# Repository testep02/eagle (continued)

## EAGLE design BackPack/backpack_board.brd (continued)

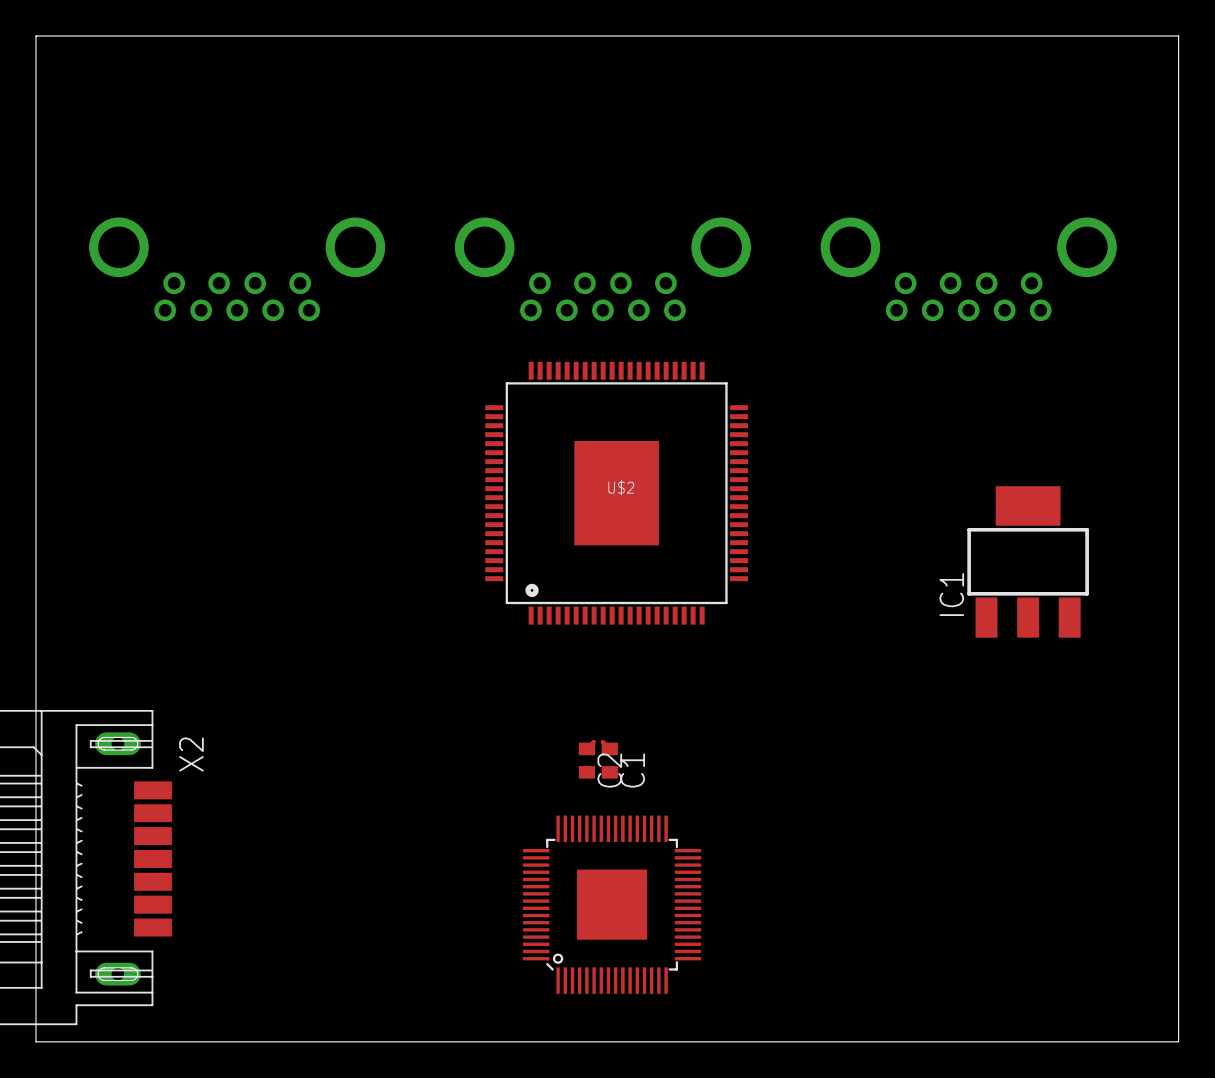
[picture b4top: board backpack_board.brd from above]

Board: 4 copper layers, 63.5 x 55.9 mm, 9 parts (0 on the bottom side), 14 nets.

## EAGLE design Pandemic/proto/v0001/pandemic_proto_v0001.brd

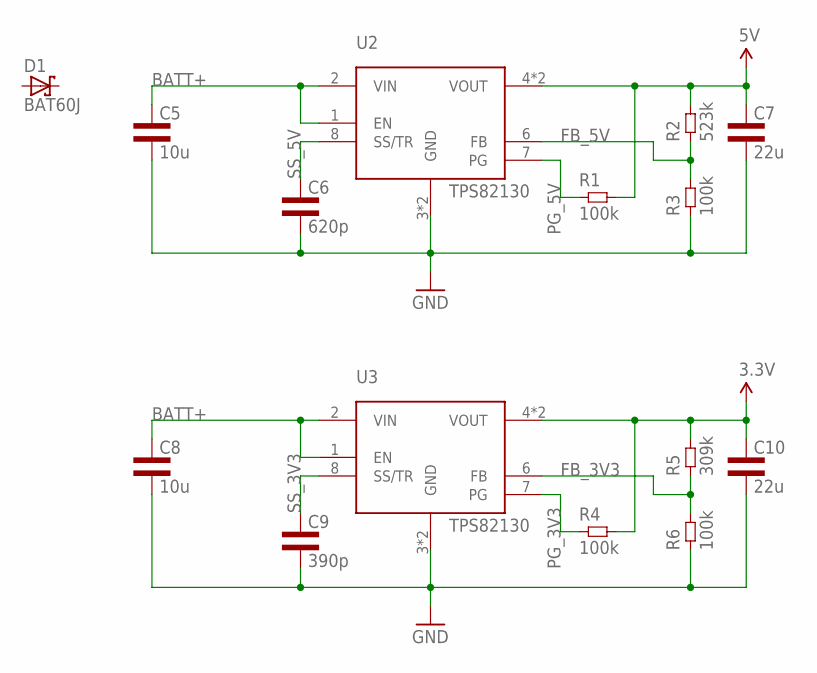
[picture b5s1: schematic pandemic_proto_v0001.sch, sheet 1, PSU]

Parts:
C5, C8: 10u; 1206L3
C6: 620p; 0402L3
C7, C10: 22u; 0805L3
C9: 390p; 0402L3
D1: BAT60J; SOD323_ST
R1, R4: 100k; 0402L3
R2: 523k; 0402L3
R3, R6: 100k; 0805L3
R5: 309k; 0402L3
U2, U3: TPS82130; SIL0008C

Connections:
3.3V: C10.1, R4.P$2 (2), R5.P$2 (2), U3.4 (VOUT), U3.5 (VOUT); also elsewhere on the board
5V: C7.1, R1.P$2 (2), R2.P$2 (2), U2.4 (VOUT), U2.5 (VOUT)
BATT+: C5.1, C8.1, U2.1 (EN), U2.2 (VIN), U3.1 (EN), U3.2 (VIN); also elsewhere on the board
FB_3V3: R5.P$1 (1), R6.2, U3.6 (FB)
FB_5V: R2.P$1 (1), R3.2, U2.6 (FB)
GND: C5.2, C6.P$2 (2), C7.2, C8.2, C9.P$2 (2), C10.2, R3.1, R6.1, U2.3 (GND), U2.TP (GND), U3.3 (GND), U3.TP (GND); also elsewhere on the board
PG_3V3: R4.P$1 (1), U3.7 (PG)
PG_5V: R1.P$1 (1), U2.7 (PG)
SS_3V3: C9.P$1 (1), U3.8 (SS/TR)
SS_5V: C6.P$1 (1), U2.8 (SS/TR)

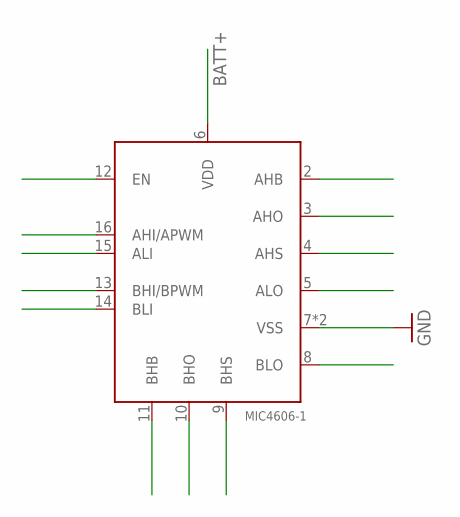
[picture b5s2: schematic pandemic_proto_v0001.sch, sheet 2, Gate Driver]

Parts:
MD1: MIC4606-1; QFN44-16LD-PL-2

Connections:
BATT+: MD1.6 (VDD); also elsewhere on the board
GND: MD1.7 (VSS), MD1.TP (VSS); also elsewhere on the board

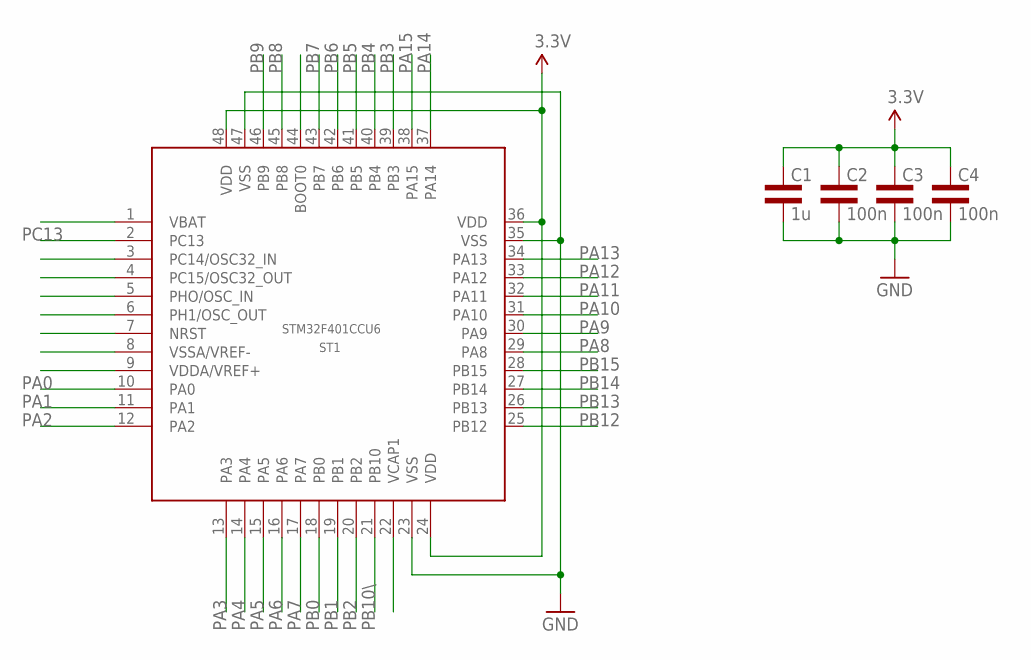
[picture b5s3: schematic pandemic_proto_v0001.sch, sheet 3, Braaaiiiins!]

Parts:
C1: 1u; 0805L3
C2, C3, C4: 100n; 0402L3
ST1: STM32F401CCU6; UFQFPN48

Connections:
3.3V: C1.1, C2.P$1 (1), C3.P$1 (1), C4.P$1 (1), ST1.24 (VDD), ST1.36 (VDD), ST1.48 (VDD); also elsewhere on the board
GND: C1.2, C2.P$2 (2), C3.P$2 (2), C4.P$2 (2), ST1.23 (VSS), ST1.35 (VSS), ST1.47 (VSS); also elsewhere on the board
PA0: ST1.10 (PA0)
PA1: ST1.11 (PA1)
PA2: ST1.12 (PA2)
PA3: ST1.13 (PA3)
PA4: ST1.14 (PA4)
PA5: ST1.15 (PA5)
PA6: ST1.16 (PA6)
PA7: ST1.17 (PA7)
PA8: ST1.29 (PA8)
PA9: ST1.30 (PA9)
PA10: ST1.31 (PA10)
PA11: ST1.32 (PA11)
PA12: ST1.33 (PA12)
PA13: ST1.34 (PA13)
PA14: ST1.37 (PA14)
PA15: ST1.38 (PA15)
PB0: ST1.18 (PB0)
PB1: ST1.19 (PB1)
PB2: ST1.20 (PB2)
PB3: ST1.39 (PB3)
PB4: ST1.40 (PB4)
PB5: ST1.41 (PB5)
PB6: ST1.42 (PB6)
PB7: ST1.43 (PB7)
PB8: ST1.45 (PB8)
PB9: ST1.46 (PB9)
PB10\: ST1.21 (PB10)
PB12: ST1.25 (PB12)
PB13: ST1.26 (PB13)
PB14: ST1.27 (PB14)
PB15: ST1.28 (PB15)
PC13: ST1.2 (PC13)

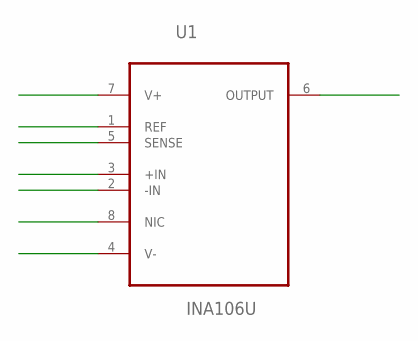
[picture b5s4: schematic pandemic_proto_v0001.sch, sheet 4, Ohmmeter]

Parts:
U1: INA106U; SOIC127P600X175-8N

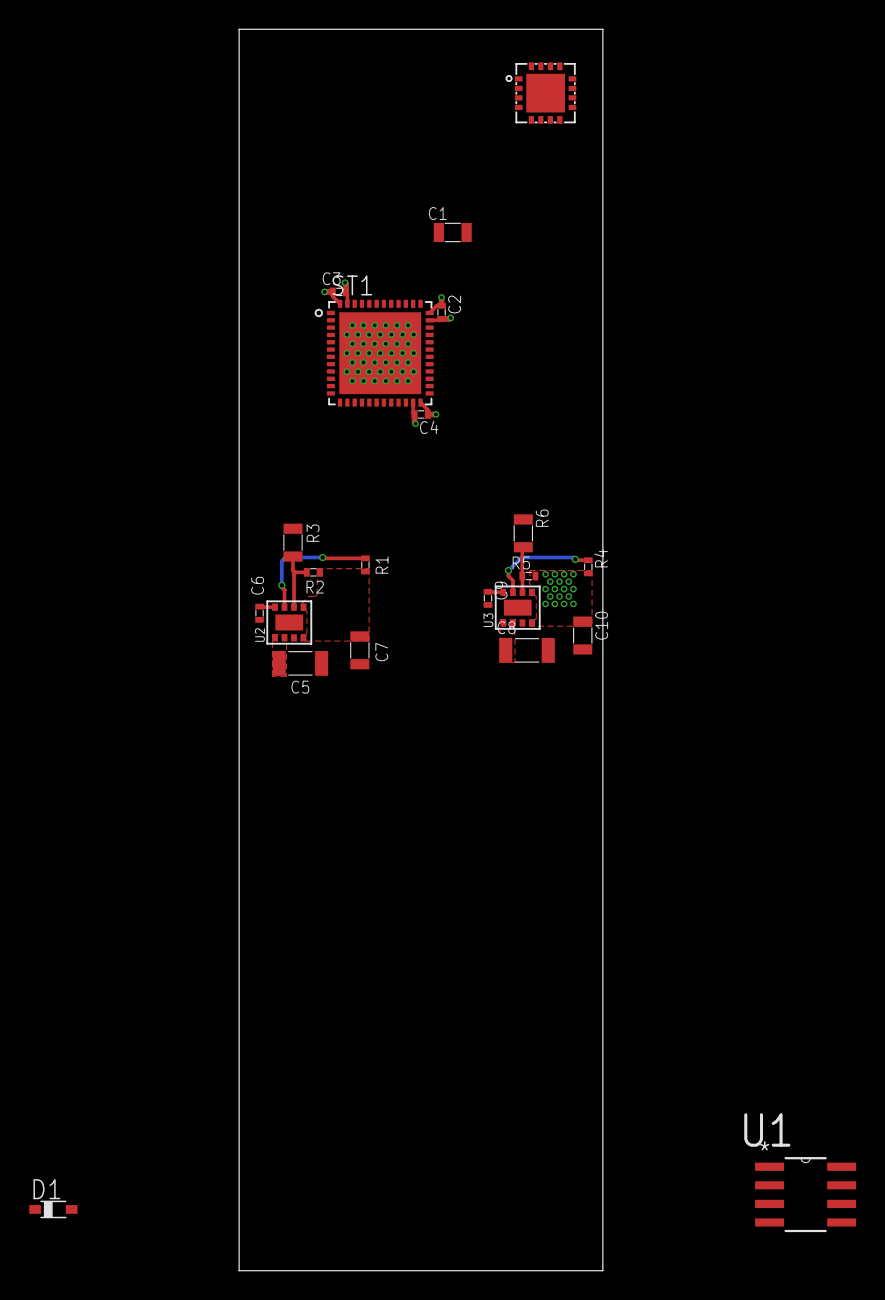
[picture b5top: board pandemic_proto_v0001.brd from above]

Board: 4 copper layers, 24.9 x 84.9 mm, 22 parts (0 on the bottom side), 10 nets.

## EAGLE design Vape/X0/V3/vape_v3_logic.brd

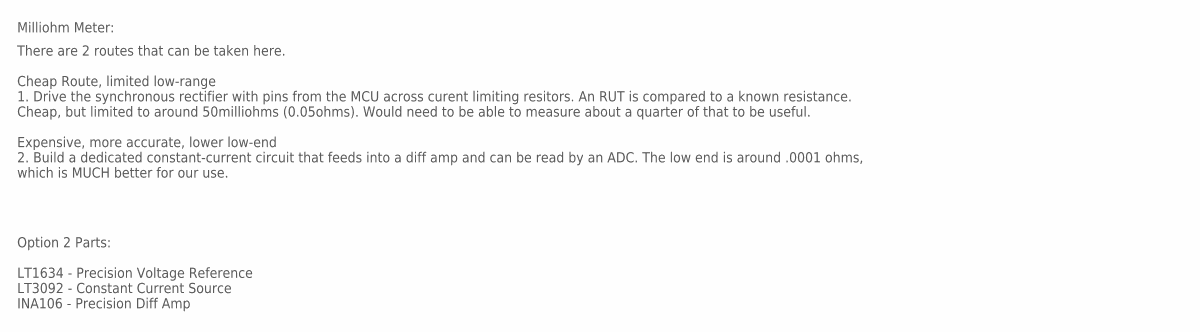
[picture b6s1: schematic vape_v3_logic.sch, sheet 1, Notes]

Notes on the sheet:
Milliohm Meter:
There are 2 routes that can be taken here. Cheap Route, limited low-range 1. Drive the synchronous rectifier with pins from the MCU across curent limiting resitors. An RUT is compared to a known resistance. Cheap, but limited to around 50milliohms (0.05ohms). Would need to be able to measure about 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
Option 2 Parts: LT1634 - Precision Voltage Reference LT3092 - Constant Current Source INA106 - Precision Diff Amp

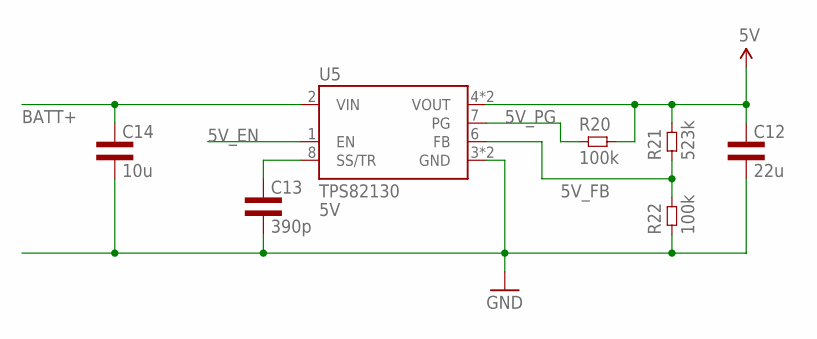
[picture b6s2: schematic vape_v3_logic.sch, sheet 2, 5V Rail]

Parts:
C12: 22u; 1206L3
C13: 390p; 0603L3
C14: 10u; 0805L3
R20: 100k; 0805L3
R21: 523k; 0603L3
R22: 100k; 0603L3
U5: TPS82130; SIL0008D

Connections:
5V: C12.1, R20.2, R21.P$2 (2), U5.4 (VOUT), U5.5 (VOUT)
5V_EN: U5.1 (EN)
5V_FB: R21.P$1 (1), R22.P$2 (2), U5.6 (FB)
5V_PG: R20.1, U5.7 (PG)
5V_SS: C13.P$1 (1), U5.8 (SS/TR)
BATT+: C14.1, U5.2 (VIN); also elsewhere on the board
GND: C12.2, C13.P$2 (2), C14.2, R22.P$1 (1), U5.3 (GND), U5.TP (GND); also elsewhere on the board

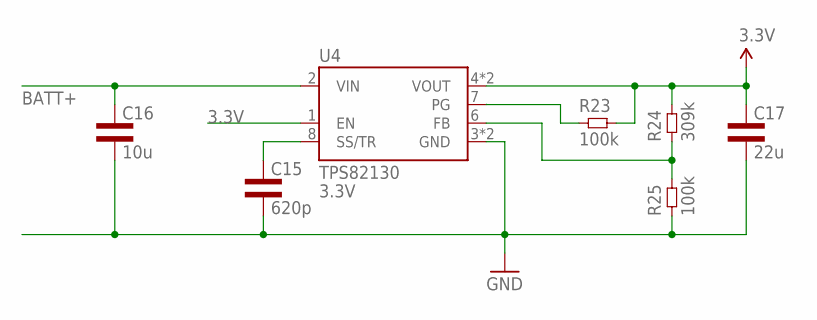
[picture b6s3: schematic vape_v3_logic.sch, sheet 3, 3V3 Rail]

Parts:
C15: 620p; 0603L3
C16: 10u; 0805L3
C17: 22u; 1206L3
R23: 100k; 0805L3
R24: 309k; 0603L3
R25: 100k; 0603L3
U4: TPS82130; SIL0008D

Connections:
3.3V: C17.1, R23.2, R24.P$2 (2), U4.1 (EN), U4.4 (VOUT), U4.5 (VOUT); also elsewhere on the board
BATT+: C16.1, U4.2 (VIN); also elsewhere on the board
GND: C15.P$2 (2), C16.2, C17.2, R25.P$1 (1), U4.3 (GND), U4.TP (GND); also elsewhere on the board
unnamed: R23.1, U4.7 (PG)
unnamed: R24.P$1 (1), R25.P$2 (2), U4.6 (FB)
unnamed: C15.P$1 (1), U4.8 (SS/TR)

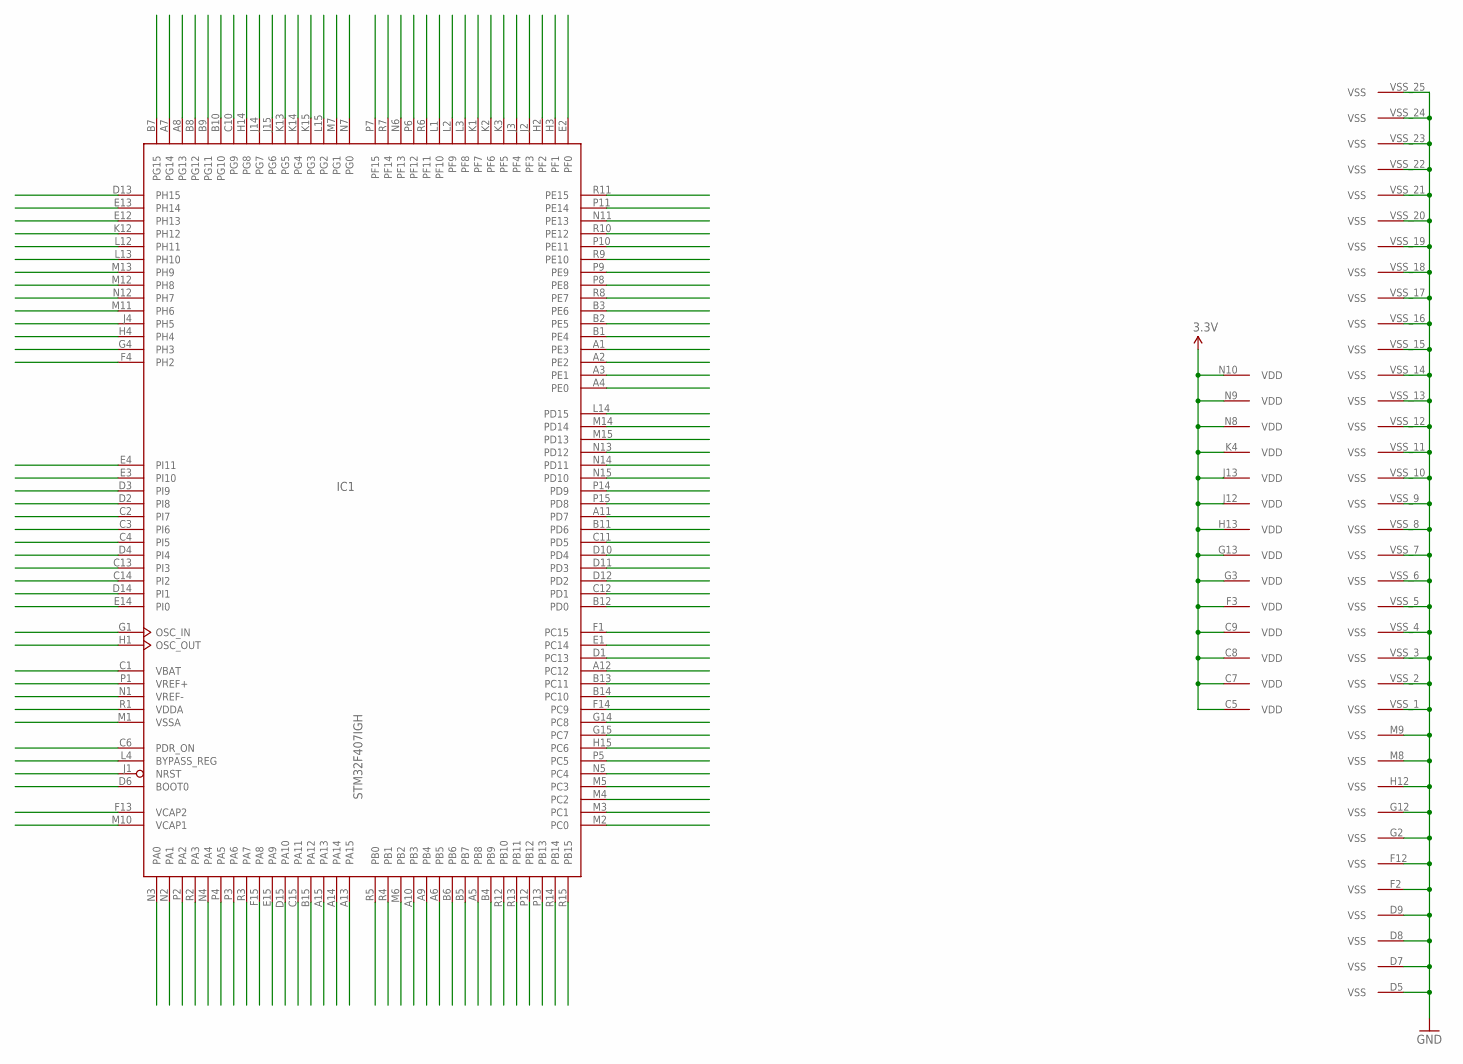
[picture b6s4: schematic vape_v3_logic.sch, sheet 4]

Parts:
IC1: STM32F407IGH; UFBGA176+25

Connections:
3.3V: IC1.C5 (VDD), IC1.C7 (VDD), IC1.C8 (VDD), IC1.C9 (VDD), IC1.F3 (VDD), IC1.G3 (VDD), IC1.G13 (VDD), IC1.H13 (VDD), IC1.J12 (VDD), IC1.J13 (VDD), IC1.K4 (VDD), IC1.N8 (VDD), IC1.N9 (VDD), IC1.N10 (VDD); also elsewhere on the board
GND: IC1.D5 (VSS), IC1.D7 (VSS), IC1.D8 (VSS), IC1.D9 (VSS), IC1.F2 (VSS), IC1.F12 (VSS), IC1.G2 (VSS), IC1.G12 (VSS), IC1.H12 (VSS), IC1.M8 (VSS), IC1.M9 (VSS), IC1.VSS_1 (VSS), IC1.VSS_2 (VSS), IC1.VSS_3 (VSS), IC1.VSS_4 (VSS), IC1.VSS_5 (VSS), IC1.VSS_6 (VSS), IC1.VSS_7 (VSS), IC1.VSS_8 (VSS), IC1.VSS_9 (VSS), IC1.VSS_10 (VSS), IC1.VSS_11 (VSS), IC1.VSS_12 (VSS), IC1.VSS_13 (VSS), IC1.VSS_14 (VSS), IC1.VSS_15 (VSS), IC1.VSS_16 (VSS), IC1.VSS_17 (VSS), IC1.VSS_18 (VSS), IC1.VSS_19 (VSS), IC1.VSS_20 (VSS), IC1.VSS_21 (VSS), IC1.VSS_22 (VSS), IC1.VSS_23 (VSS), IC1.VSS_24 (VSS), IC1.VSS_25 (VSS); also elsewhere on the board

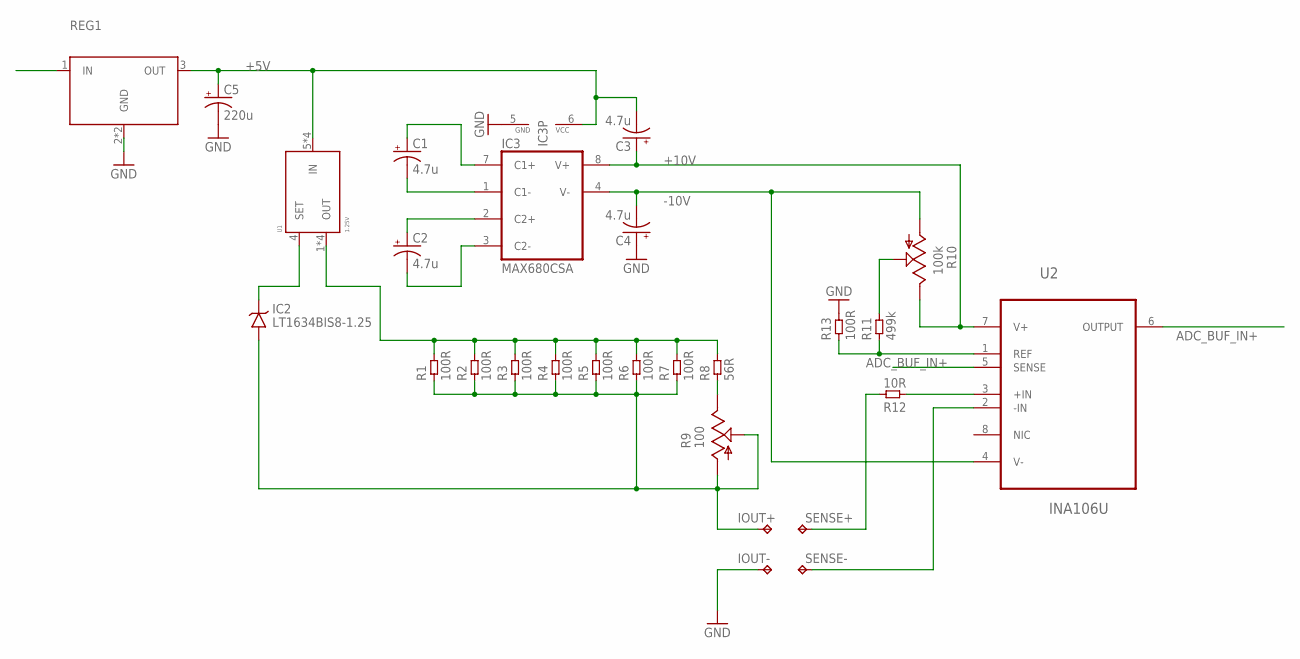
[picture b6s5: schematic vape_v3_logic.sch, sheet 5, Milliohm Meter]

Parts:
C1, C2, C3, C4: 4.7u; B/3528-21R; PART# T521B475M035ATE150
C5: 220u; PANASONIC_C
IC2: LT1634BIS8-1.25; S8
IC3: MAX680CSA; SO08
IOUT+: TPPAD1-17; P1-17
IOUT-: TPPAD1-17; P1-17
R1, R2, R3, R4, R5, R6, R7: 100R; 0603L3; PART# APC0603T100RZ
R8: 56R; 0603L3; PART# APC0603T100RZ
R9: 100; 3223W
R10: 100k; 3223W
R11: 499k; 0603L3
R12: 10R; 0603L3
R13: 100R; 0603L3
REG1: LDO_REG_4PIN; SOT-223-3
SENSE+: TPPAD1-17; P1-17
SENSE-: TPPAD1-17; P1-17
U1: 1.25V; DD-8
U2: INA106U; SOIC127P600X175-8N

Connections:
+5V: C3.-, C5.+, IC3.6 (VCC), REG1.3 (OUT), U1.5 (IN), U1.6 (IN), U1.7 (IN), U1.8 (IN)
+10V: C3.+, IC3.8 (V+), R10.3 (E), U2.7 (V+)
-10V: C4.-, IC3.4 (V-), R10.1 (A), U2.4 (V-)
ADC_BUF_IN+: U2.5 (SENSE), U2.6 (OUTPUT); also elsewhere on the board
CC: IC2.4 (GND), IOUT+.TP, R1.P$1 (1), R2.P$1 (1), R3.P$1 (1), R4.P$1 (1), R5.P$1 (1), R6.P$1 (1), R7.P$1 (1), R9.1 (A), R9.2 (S)
CC_OUT: R1.P$2 (2), R2.P$2 (2), R3.P$2 (2), R4.P$2 (2), R5.P$2 (2), R6.P$2 (2), R7.P$2 (2), R8.P$2 (2), U1.1 (OUT), U1.2 (OUT), U1.3 (OUT), U1.9 (OUT)
GND: C4.+, C5.-, IC3.5 (GND), IOUT-.TP, R13.P$2 (2), REG1.2 (GND), REG1.4 (GND); also elsewhere on the board
MEAS_NEG: SENSE-.TP, U2.2 (-IN)
MEAS_POS: R12.P$2 (2), SENSE+.TP
unnamed: IC2.6 (VOUT), U1.4 (SET)
unnamed: C1.-, IC3.1 (C1-)
unnamed: C2.+, IC3.2 (C2+)
unnamed: C1.+, IC3.7 (C1+)
unnamed: C2.-, IC3.3 (C2-)
unnamed: R12.P$1 (1), U2.3 (+IN)
unnamed: R8.P$1 (1), R9.3 (E)
unnamed: R11.P$1 (1), R13.P$1 (1), U2.1 (REF)
unnamed: R10.2 (S), R11.P$2 (2)
V_IN: REG1.1 (IN)

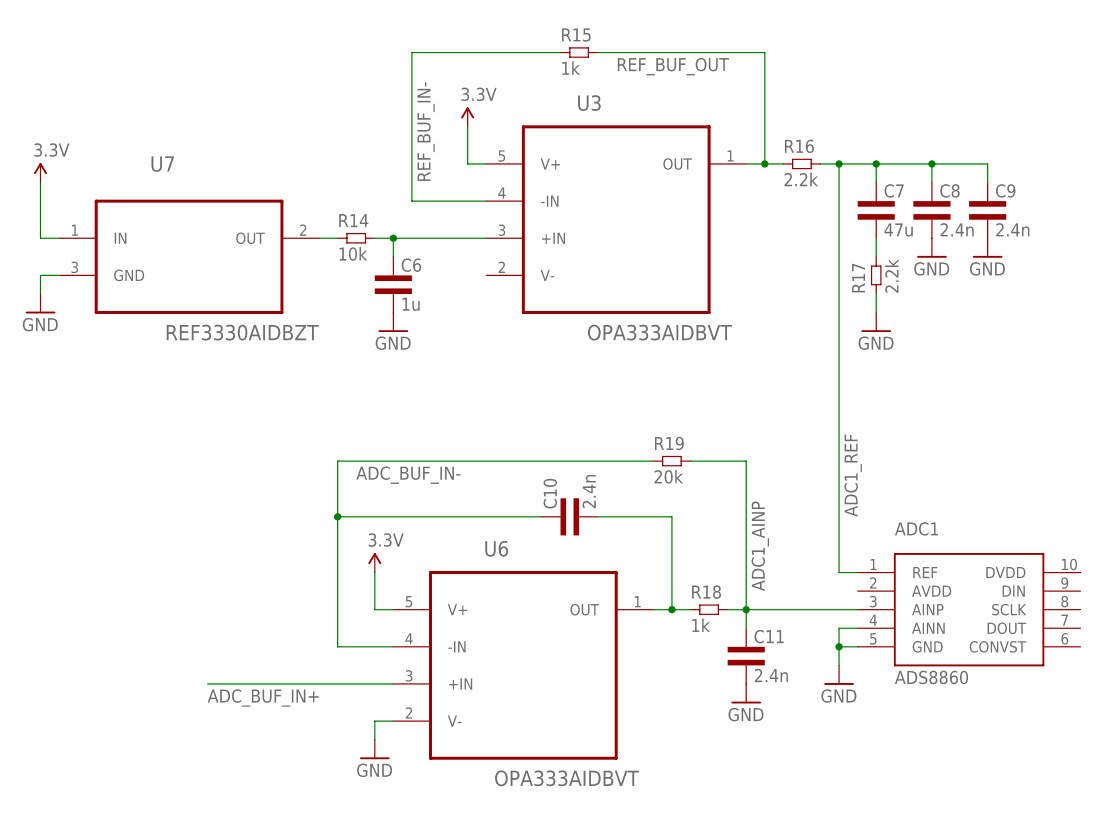
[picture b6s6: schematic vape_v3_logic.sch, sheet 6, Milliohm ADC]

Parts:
ADC1: ADS8860IDGSR; S-PDSO-G10
C6: 1u; 0603L3
C7: 47u; 0805L3; PART# C2012JB1A476M125AC
C8, C9, C10, C11: 2.4n; 0603L3
R14: 10k; 0603L3
R15, R18: 1k; 0603L3
R16, R17: 2.2k; 0603L3
R19: 20k; 0603L3
U3, U6: OPA333AIDBVT; SOT95P280X145-5N
U7: REF3330AIDBZT; SOT95P237X112-3N

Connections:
3.3V: U3.5 (V+), U6.5 (V+), U7.1 (IN); also elsewhere on the board
ADC1_AINP: ADC1.3 (AINP), C11.P$1 (1), R18.P$2 (2), R19.P$2 (2)
ADC1_REF: ADC1.1 (REF), C7.1, C8.P$1 (1), C9.P$1 (1), R16.P$2 (2)
ADC_BUF_IN+: U6.3 (+IN); also elsewhere on the board
ADC_BUF_IN-: C10.P$1 (1), R19.P$1 (1), U6.4 (-IN)
ADC_BUF_OUT: C10.P$2 (2), R18.P$1 (1), U6.1 (OUT)
GND: ADC1.4 (AINN), ADC1.5 (GND), C6.P$2 (2), C8.P$2 (2), C9.P$2 (2), C11.P$2 (2), R17.P$1 (1), U6.2 (V-), U7.3 (GND); also elsewhere on the board
unnamed: C7.2, R17.P$2 (2)
REF_BUF_IN+: C6.P$1 (1), R14.P$2 (2), U3.3 (+IN)
REF_BUF_IN-: R15.P$1 (1), U3.4 (-IN)
REF_BUF_OUT: R15.P$2 (2), R16.P$1 (1), U3.1 (OUT)
REF_OUT: R14.P$1 (1), U7.2 (OUT)
V-: U3.2 (V-)

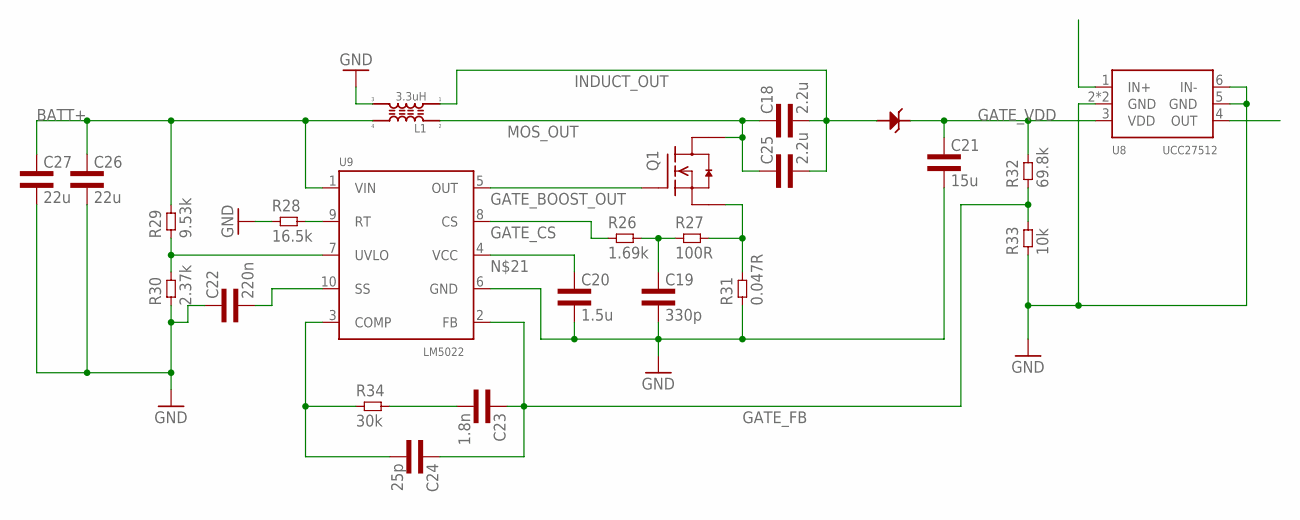
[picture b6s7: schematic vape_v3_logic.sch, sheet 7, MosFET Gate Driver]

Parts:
C18, C25: 2.2u; 0402L3
C19: 330p; 0402L3
C20: 1.5u; 0402L3
C21: 15u; 1206L3
C22: 220n; 0402L3
C23: 1.8n; 0402L3
C24: 25p; 0402L3
C26, C27: 22u; 1206L3
D1: .77V / 5.5A; DPAK
L1: 3.3uH; DRQ12X
Q1: OPEN-BLDC_FDMC7664; OPEN-BLDC_MLP33
R26: 1.69k; 0402L3
R27: 100R; 0402L3
R28: 16.5k; 0402L3
R29: 9.53k; 0402L3
R30: 2.37k; 0402L3
R31: 0.047R; 1206L3
R32: 69.8k; 0402L3
R33: 10k; 0402L3
R34: 30k; 0402L3
U8: UCC27512; S-PWSON-N6
U9: LM5022; S-PDSO-G10

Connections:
BATT+: C26.1, C27.1, L1.4, R29.P$2 (2), U9.1 (VIN); also elsewhere on the board
GATE_BOOST_OUT: Q1.4G (G), U9.5 (OUT)
GATE_COMP: C24.P$2 (2), R34.P$1 (1), U9.3 (COMP)
GATE_CS: R26.P$1 (1), U9.8 (CS)
GATE_FB: C23.P$1 (1), C24.P$1 (1), R32.P$1 (1), R33.P$2 (2), U9.2 (FB)
GATE_SS: C22.P$2 (2), U9.10 (SS)
GATE_UVLO: R29.P$1 (1), R30.P$2 (2), U9.7 (UVLO)
GATE_VDD: C21.1, D1.TAB (CATHODE), R32.P$2 (2), U8.3 (VDD)
GND: C19.P$2 (2), C20.P$2 (2), C21.2, C22.P$1 (1), C26.2, C27.2, L1.3, R28.P$1 (1), R30.P$1 (1), R31.1, R33.P$1 (1), U8.2 (GND), U8.5 (GND), U8.6 (IN-), U8.TP (GND), U9.6 (GND); also elsewhere on the board
INDUCT_OUT: C18.P$2 (2), C25.P$2 (2), D1.1 (ANODE), D1.3 (ANODE), L1.1
MOS_OUT: C18.P$1 (1), C25.P$1 (1), L1.2, Q1.5678D (D)
unnamed: C19.P$1 (1), R26.P$2 (2), R27.P$1 (1)
unnamed: Q1.123S (S), R27.P$2 (2), R31.2
unnamed: C20.P$1 (1), U9.4 (VCC)
unnamed: R28.P$2 (2), U9.9 (RT)
unnamed: C23.P$2 (2), R34.P$2 (2)

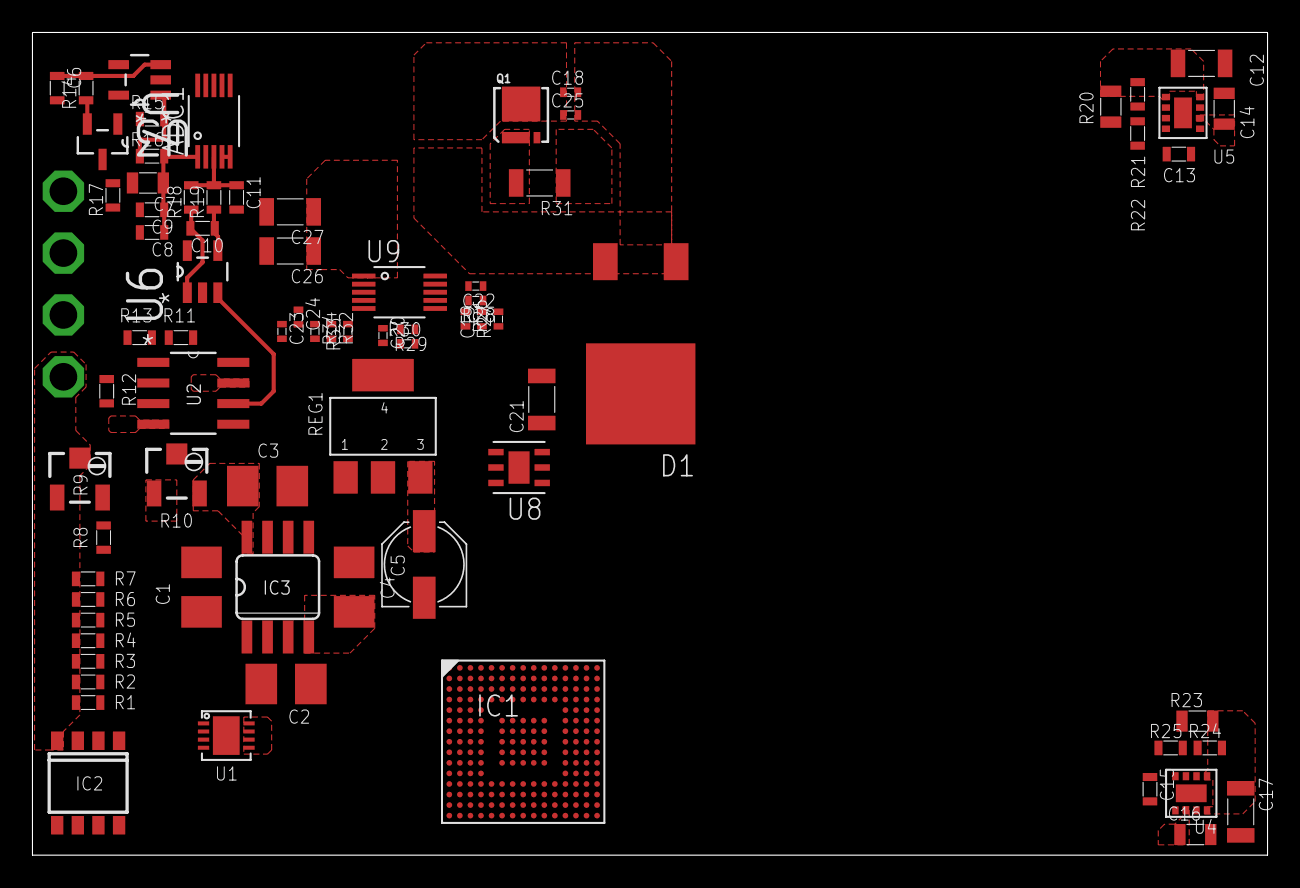
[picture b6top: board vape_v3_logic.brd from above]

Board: 4 copper layers, 76.1 x 50.7 mm, 82 parts (1 on the bottom side), 50 nets.

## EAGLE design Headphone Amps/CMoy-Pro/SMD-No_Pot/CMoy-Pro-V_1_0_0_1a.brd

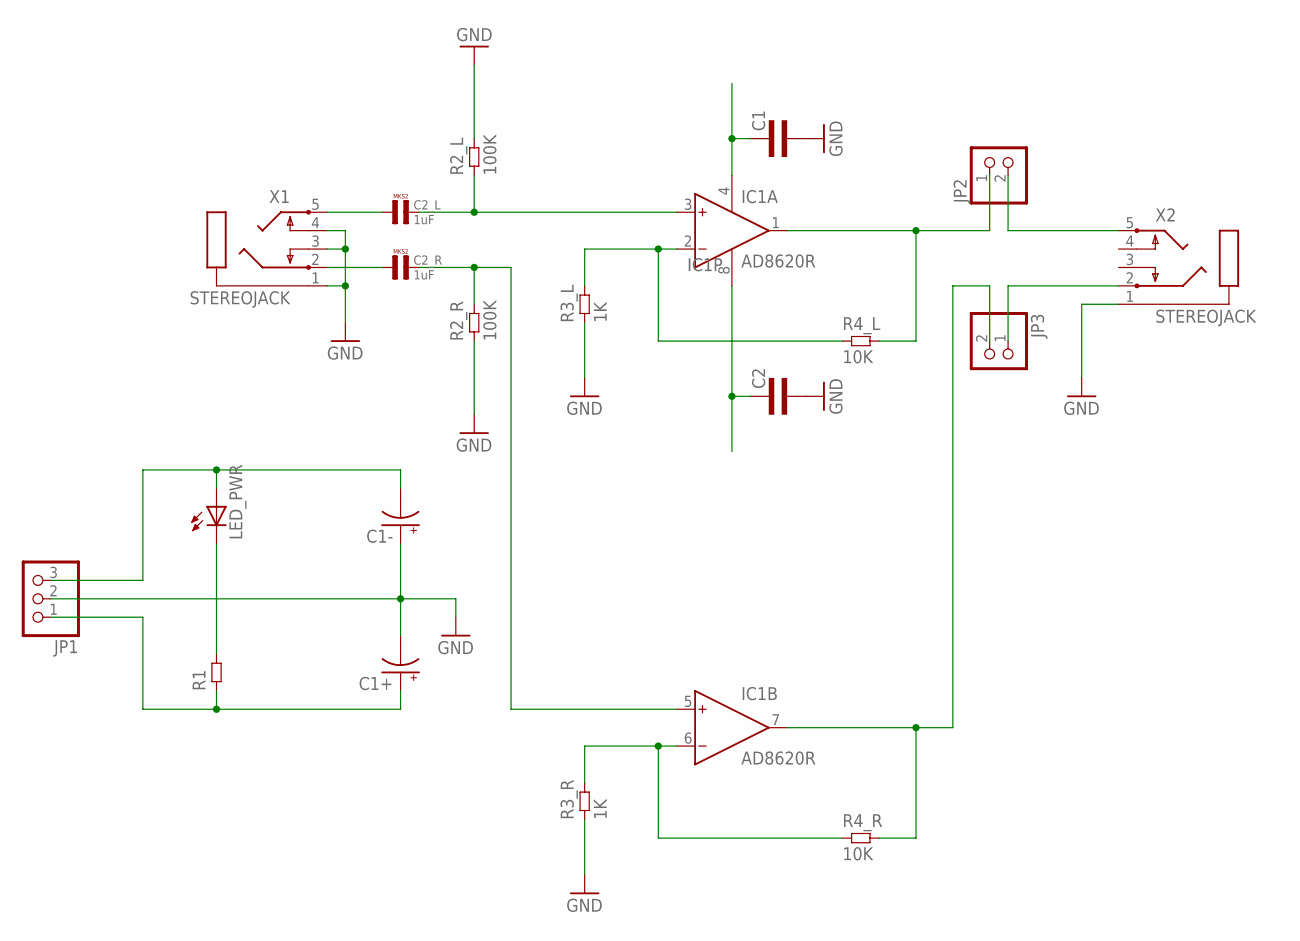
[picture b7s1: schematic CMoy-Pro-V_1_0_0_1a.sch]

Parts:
C1, C2: CAP0603L3; 0603L3
C1+, C1-: CPOL-US140CLH-1010; 140CLH-1010
C2_L, C2_R: 1uF; R5B5
IC1: AD8620R; SO8
JP1: PINHD-1X3; 1X03
JP2, JP3: PINHD-1X2; 1X02
LED_PWR: LEDCHIP-LED0603; CHIP-LED0603
R1: RES0603L3; 0603L3
R2_L, R2_R: 100K; 0603L3
R3_L, R3_R: 1K; 0603L3
R4_L, R4_R: 10K; 0603L3
X1, X2: STEREOJACK; STX3100

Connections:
GND: C1.P$2 (2), C1+.-, C1-.+, C2.P$2 (2), JP1.2, R2_L.P$2 (2), R2_R.P$1 (1), R3_L.P$1 (1), R3_R.P$1 (1), X1.1, X1.3, X1.4, X2.1
HP_L: C2_R.1, X1.2
HP_R: C2_L.1, X1.5
IN_L: C2_R.2, IC1.5 (IN+), R2_R.P$2 (2)
IN_R: C2_L.2, IC1.3 (IN+), R2_L.P$1 (1)
unnamed: LED_PWR.C, R1.P$2 (2)
unnamed: JP2.2, X2.5
unnamed: JP3.1, X2.2
unnamed: IC1.2 (IN-), R3_L.P$2 (2), R4_L.P$1 (1)
unnamed: IC1.6 (IN-), R3_R.P$2 (2), R4_R.P$1 (1)
OUT_L: IC1.1 (OUT), JP2.1, R4_L.P$2 (2)
OUT_R: IC1.7 (OUT), JP3.2, R4_R.P$2 (2)
V+: C1+.+, C2.P$1 (1), IC1.8 (V+), JP1.1, R1.P$1 (1)
V-: C1.P$1 (1), C1-.-, IC1.4 (V-), JP1.3, LED_PWR.A

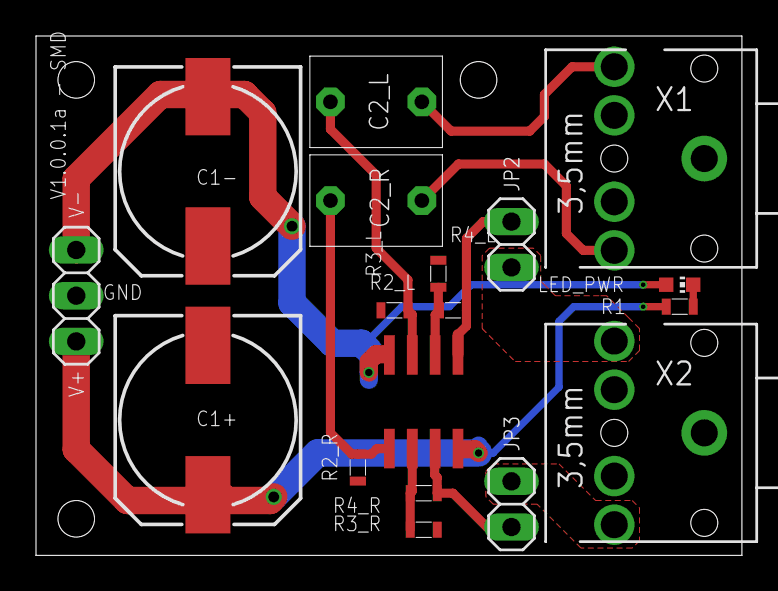
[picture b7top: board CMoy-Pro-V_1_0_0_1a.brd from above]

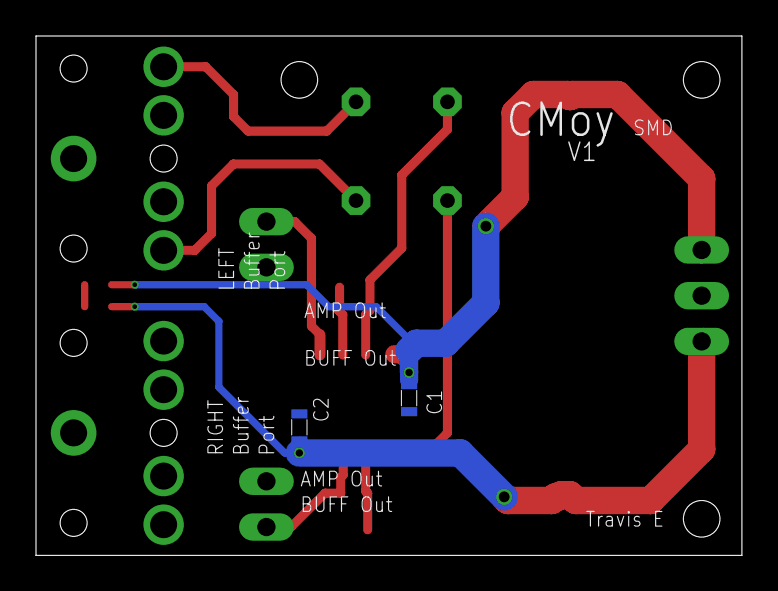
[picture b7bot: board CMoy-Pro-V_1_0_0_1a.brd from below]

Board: 2 copper layers, 39.2 x 28.9 mm, 20 parts (2 on the bottom side), 14 nets.

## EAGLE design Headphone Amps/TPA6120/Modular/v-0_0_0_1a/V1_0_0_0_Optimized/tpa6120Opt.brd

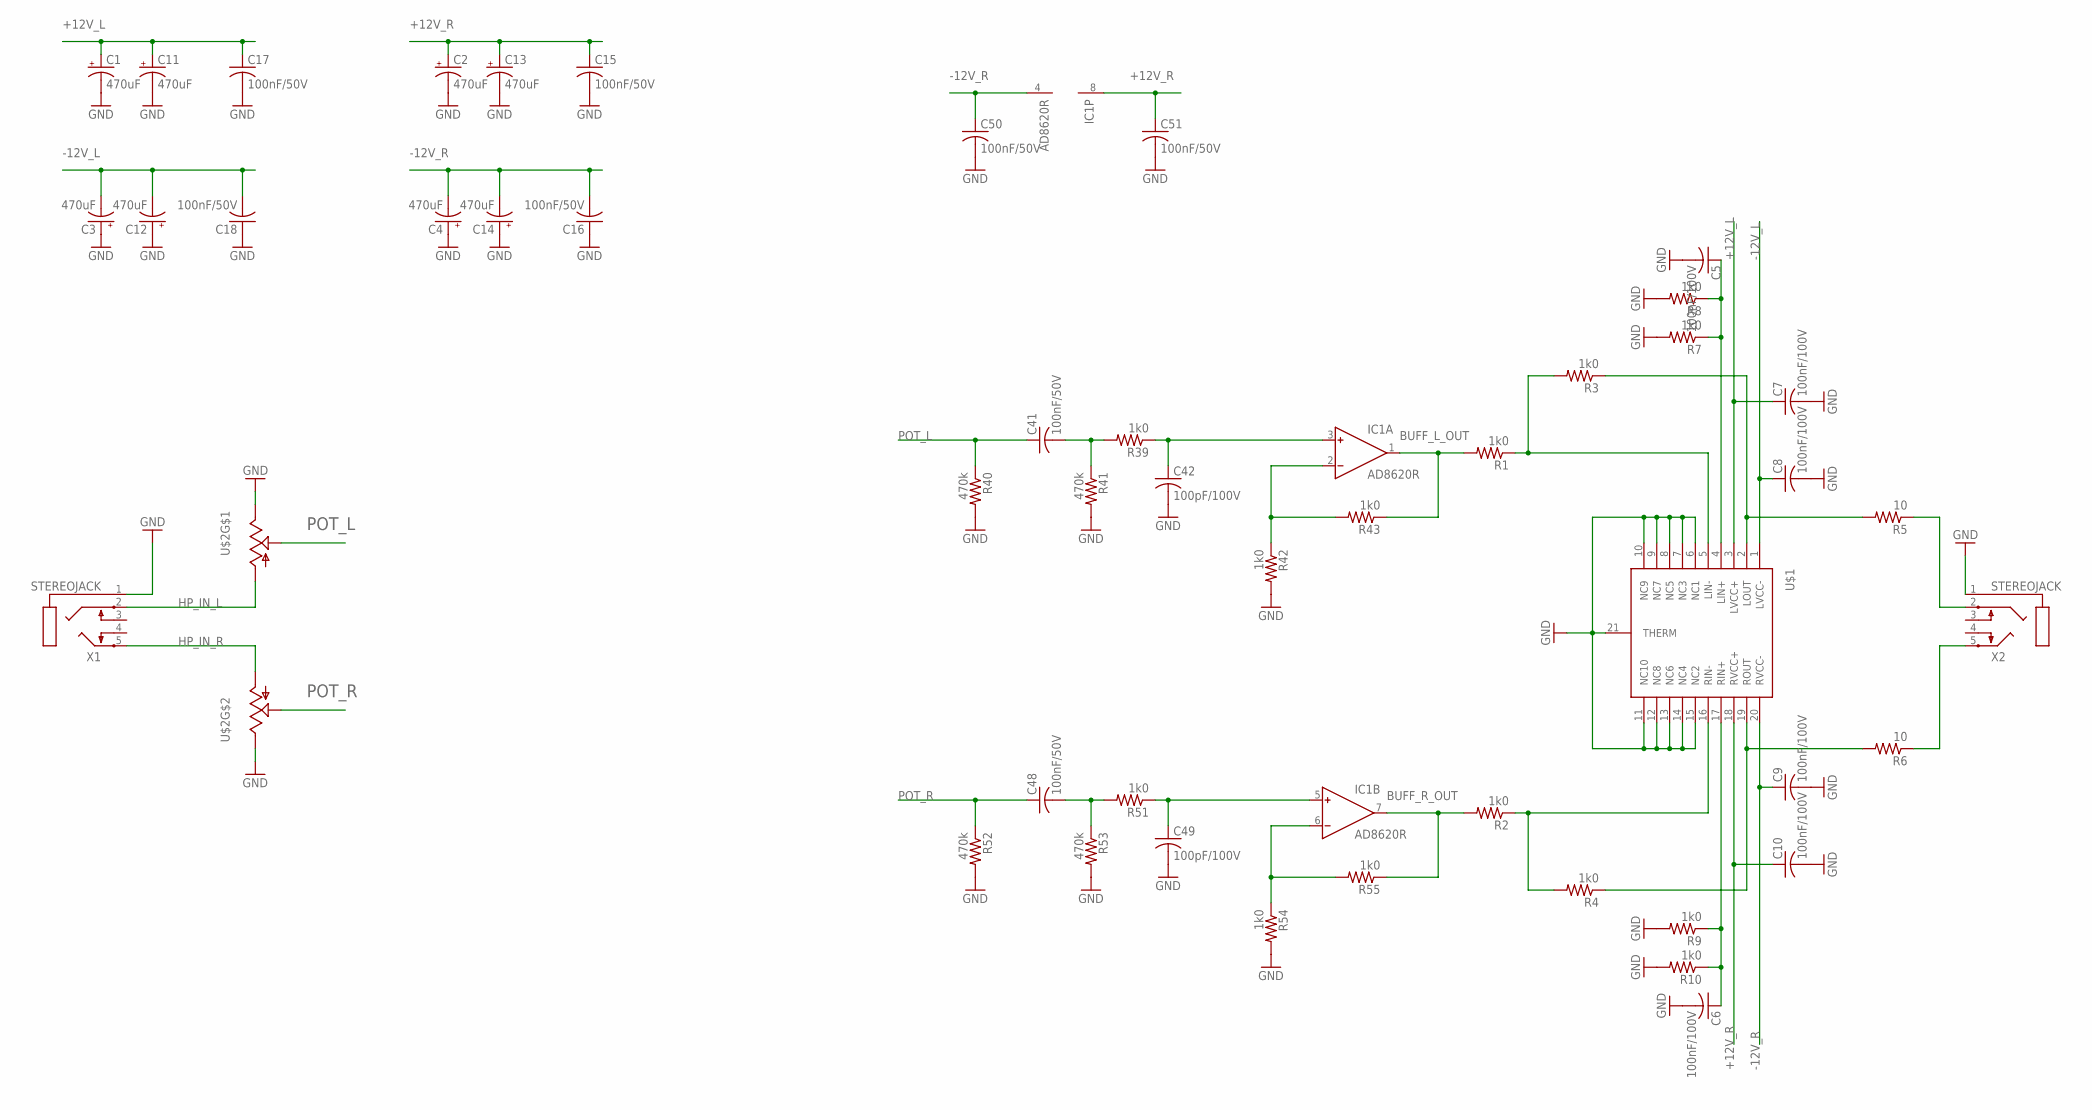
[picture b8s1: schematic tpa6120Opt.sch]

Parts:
C1, C2, C3, C4, C11, C12, C13, C14: 470uF; E5-13
C5, C6, C7, C8, C9, C10: 100nF/100V; C0402
C15, C16, C17, C18, C50, C51: 100nF/50V; C0402K
C41, C48: 100nF/50V; C0805
C42, C49: 100pF/100V; C0805
IC1: AD8620R; SO8
R1, R2, R3, R4, R7, R8, R9, R10: 1k0; R0402
R5, R6: 10; R0402
R39, R42, R43, R51, R54, R55: 1k0; M0805
R40, R41, R52, R53: 470k; M0805
U$1: TPA6120_TPA6120
U$2: ALPS_BLUE; ALPS_RK27
X1, X2: STEREOJACK; STX3100

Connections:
+12V_L: C1.+, C7.1, C11.+, C17.1, U$1.3 (LVCC+)
+12V_R: C2.+, C10.1, C13.+, C15.1, C51.1, IC1.8 (V+), U$1.18 (RVCC+)
-12V_L: C3.-, C8.1, C12.-, C18.2, U$1.1 (LVCC-)
-12V_R: C4.-, C9.1, C14.-, C16.2, C50.1, IC1.4 (V-), U$1.20 (RVCC-)
BUFF_L_OUT: IC1.1 (OUT), R1.2, R43.1
BUFF_R_OUT: IC1.7 (OUT), R2.2, R55.1
GND: C1.-, C2.-, C3.+, C4.+, C5.2, C6.2, C7.2, C8.2, C9.2, C10.2, C11.-, C12.+, C13.-, C14.+, C15.2, C16.1, C17.2, C18.1, C42.2, C49.2, C50.2, C51.2, R7.2, R8.2, R9.2, R10.2, R40.2, R41.2, R42.2, R52.2, R53.2, R54.2, U$1.6 (NC1), U$1.7 (NC3), U$1.8 (NC5), U$1.9 (NC7), U$1.10 (NC9), U$1.11 (NC10), U$1.12 (NC8), U$1.13 (NC6), U$1.14 (NC4), U$1.15 (NC2), U$1.21 (THERM), U$2.I1 (3), U$2.I2 (3), X1.1, X2.1
HP_IN_L: U$2.G1 (1), X1.2
HP_IN_R: U$2.G2 (1), X1.5
INVERT_L: R1.1, R3.2, U$1.5 (LIN-)
INVERT_R: R2.1, R4.2, U$1.16 (RIN-)
unnamed: C5.1, R7.1, R8.1, U$1.4 (LIN+)
unnamed: C6.1, R9.1, R10.1, U$1.17 (RIN+)
unnamed: R6.1, X2.5
unnamed: R5.1, X2.2
unnamed: C41.2, R39.2, R41.1
unnamed: C42.1, IC1.3 (IN+), R39.1
unnamed: IC1.2 (IN-), R42.1, R43.2
unnamed: C48.2, R51.2, R53.1
unnamed: C49.1, IC1.5 (IN+), R51.1
unnamed: IC1.6 (IN-), R54.1, R55.2
OUT_L: R3.1, R5.2, U$1.2 (LOUT)
OUT_R: R4.1, R6.2, U$1.19 (ROUT)
POT_L: C41.1, R40.1, U$2.O1 (2)
POT_R: C48.1, R52.1, U$2.O2 (2)

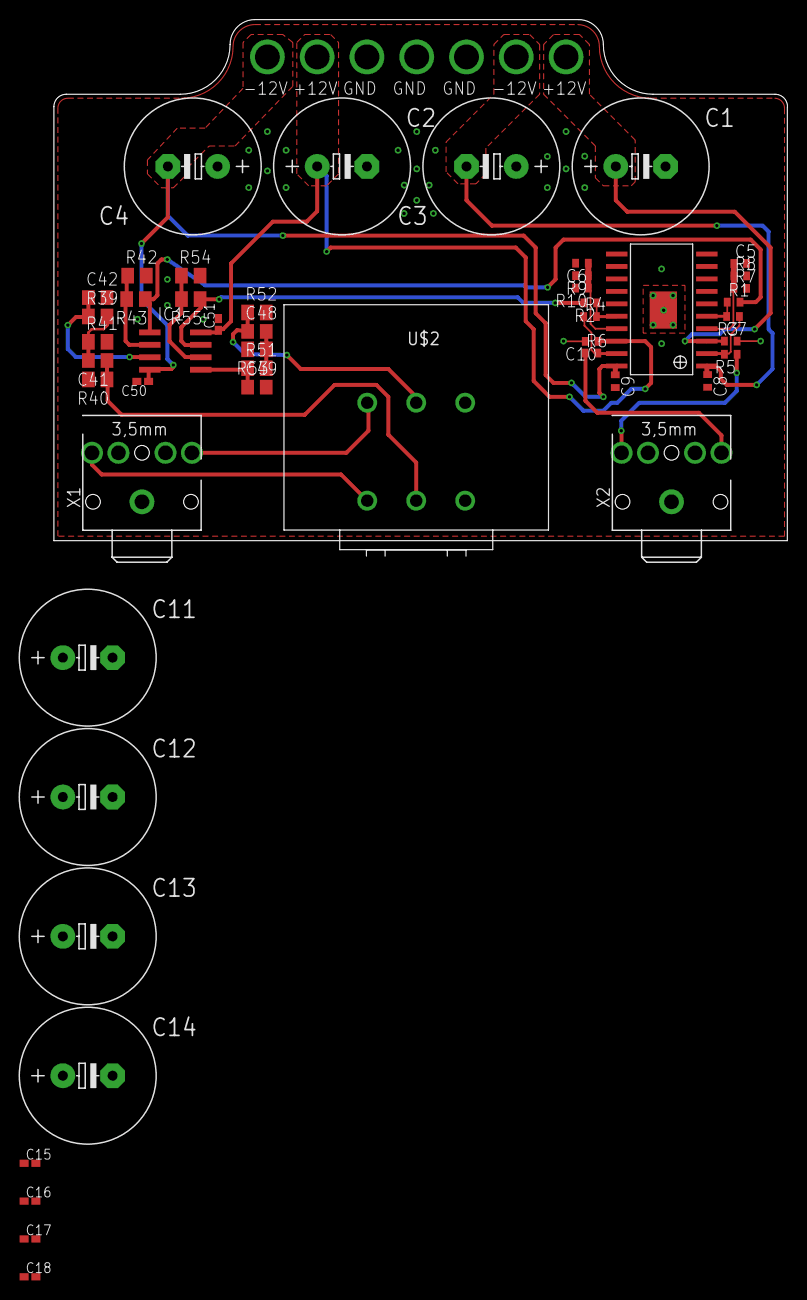
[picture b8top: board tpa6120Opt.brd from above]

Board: 2 copper layers, 74.9 x 53.2 mm, 49 parts (0 on the bottom side), 25 nets.

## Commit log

2019-05-16 Changes from surface book
    These are the files that have changed on the surface book. I have not tracked the project individually.
2019-12-09 Several Projects
    Projects - Vape - USB Microphone - USB Hub - Headphone Amps - Backpack
